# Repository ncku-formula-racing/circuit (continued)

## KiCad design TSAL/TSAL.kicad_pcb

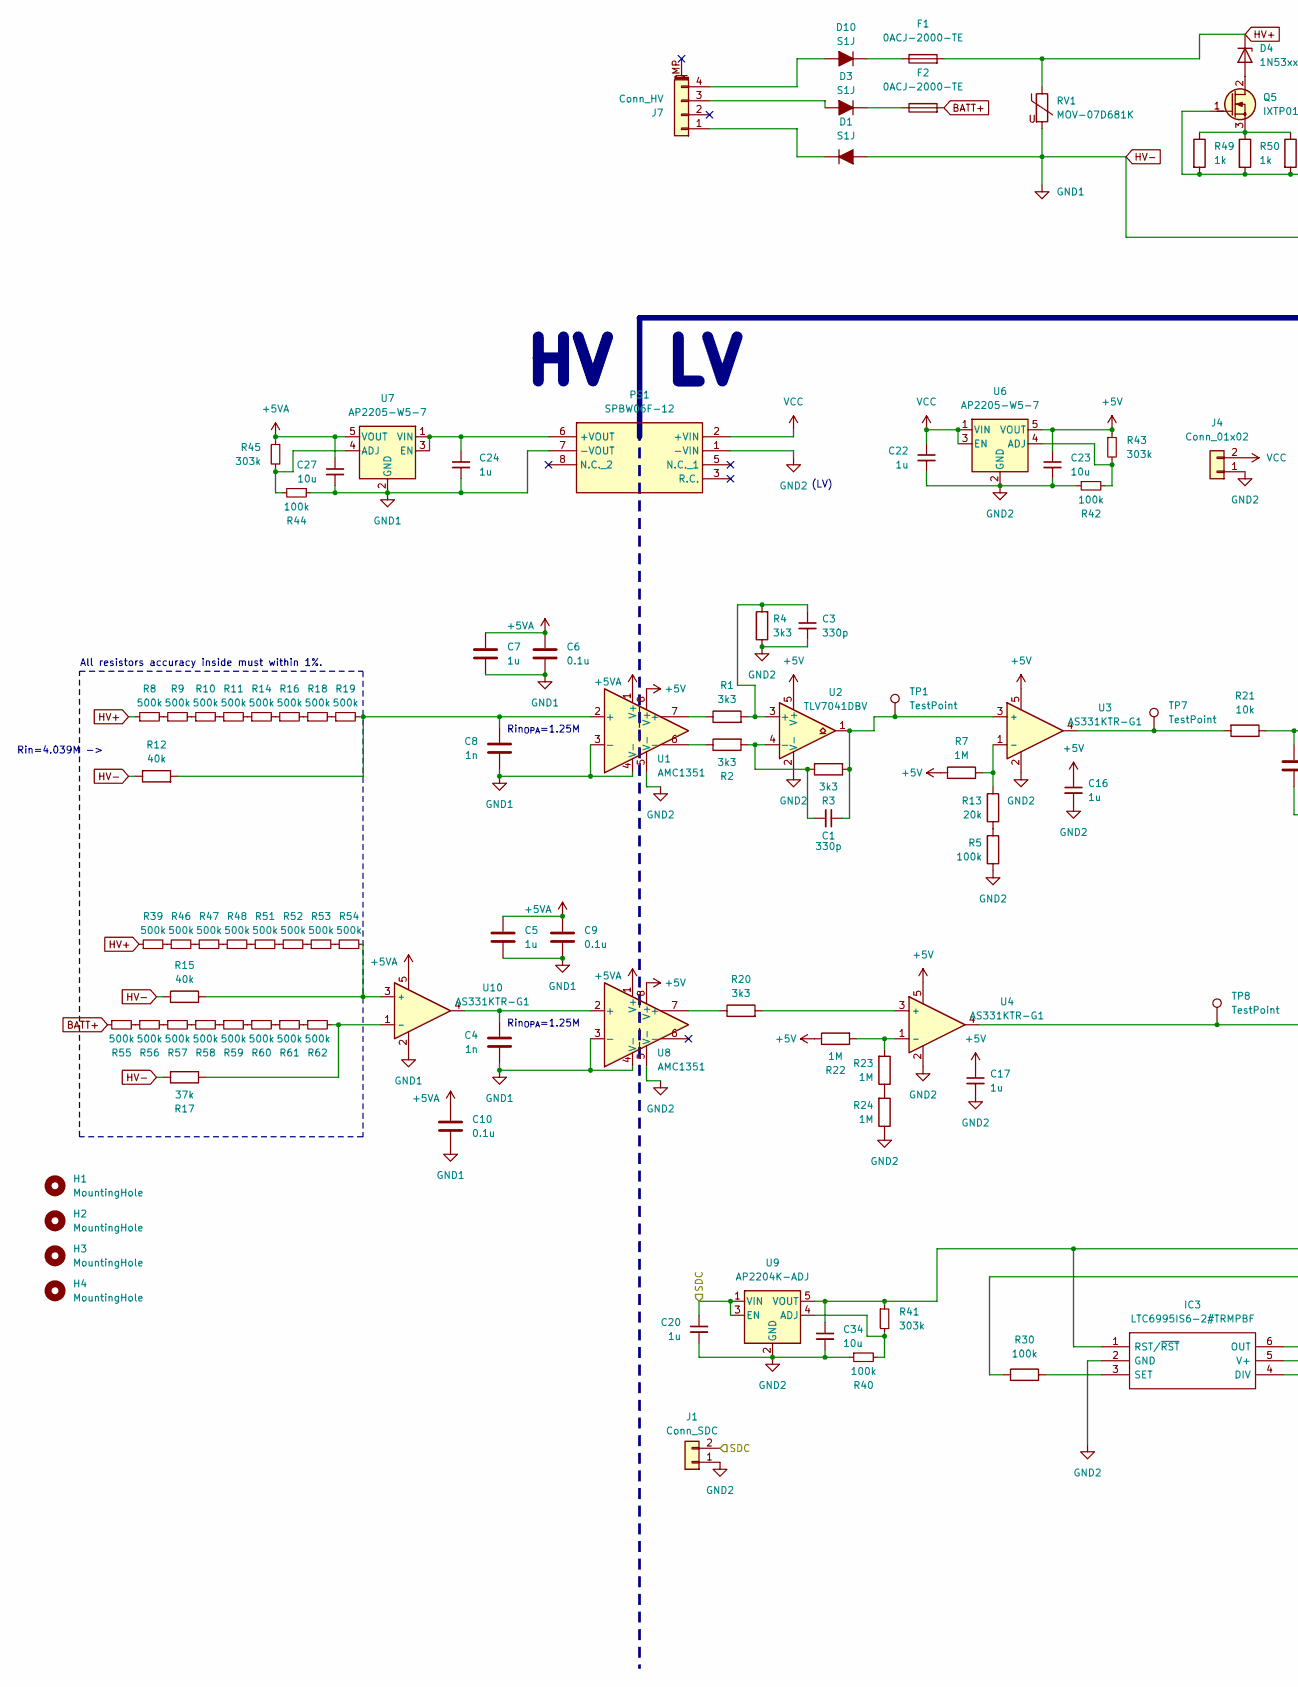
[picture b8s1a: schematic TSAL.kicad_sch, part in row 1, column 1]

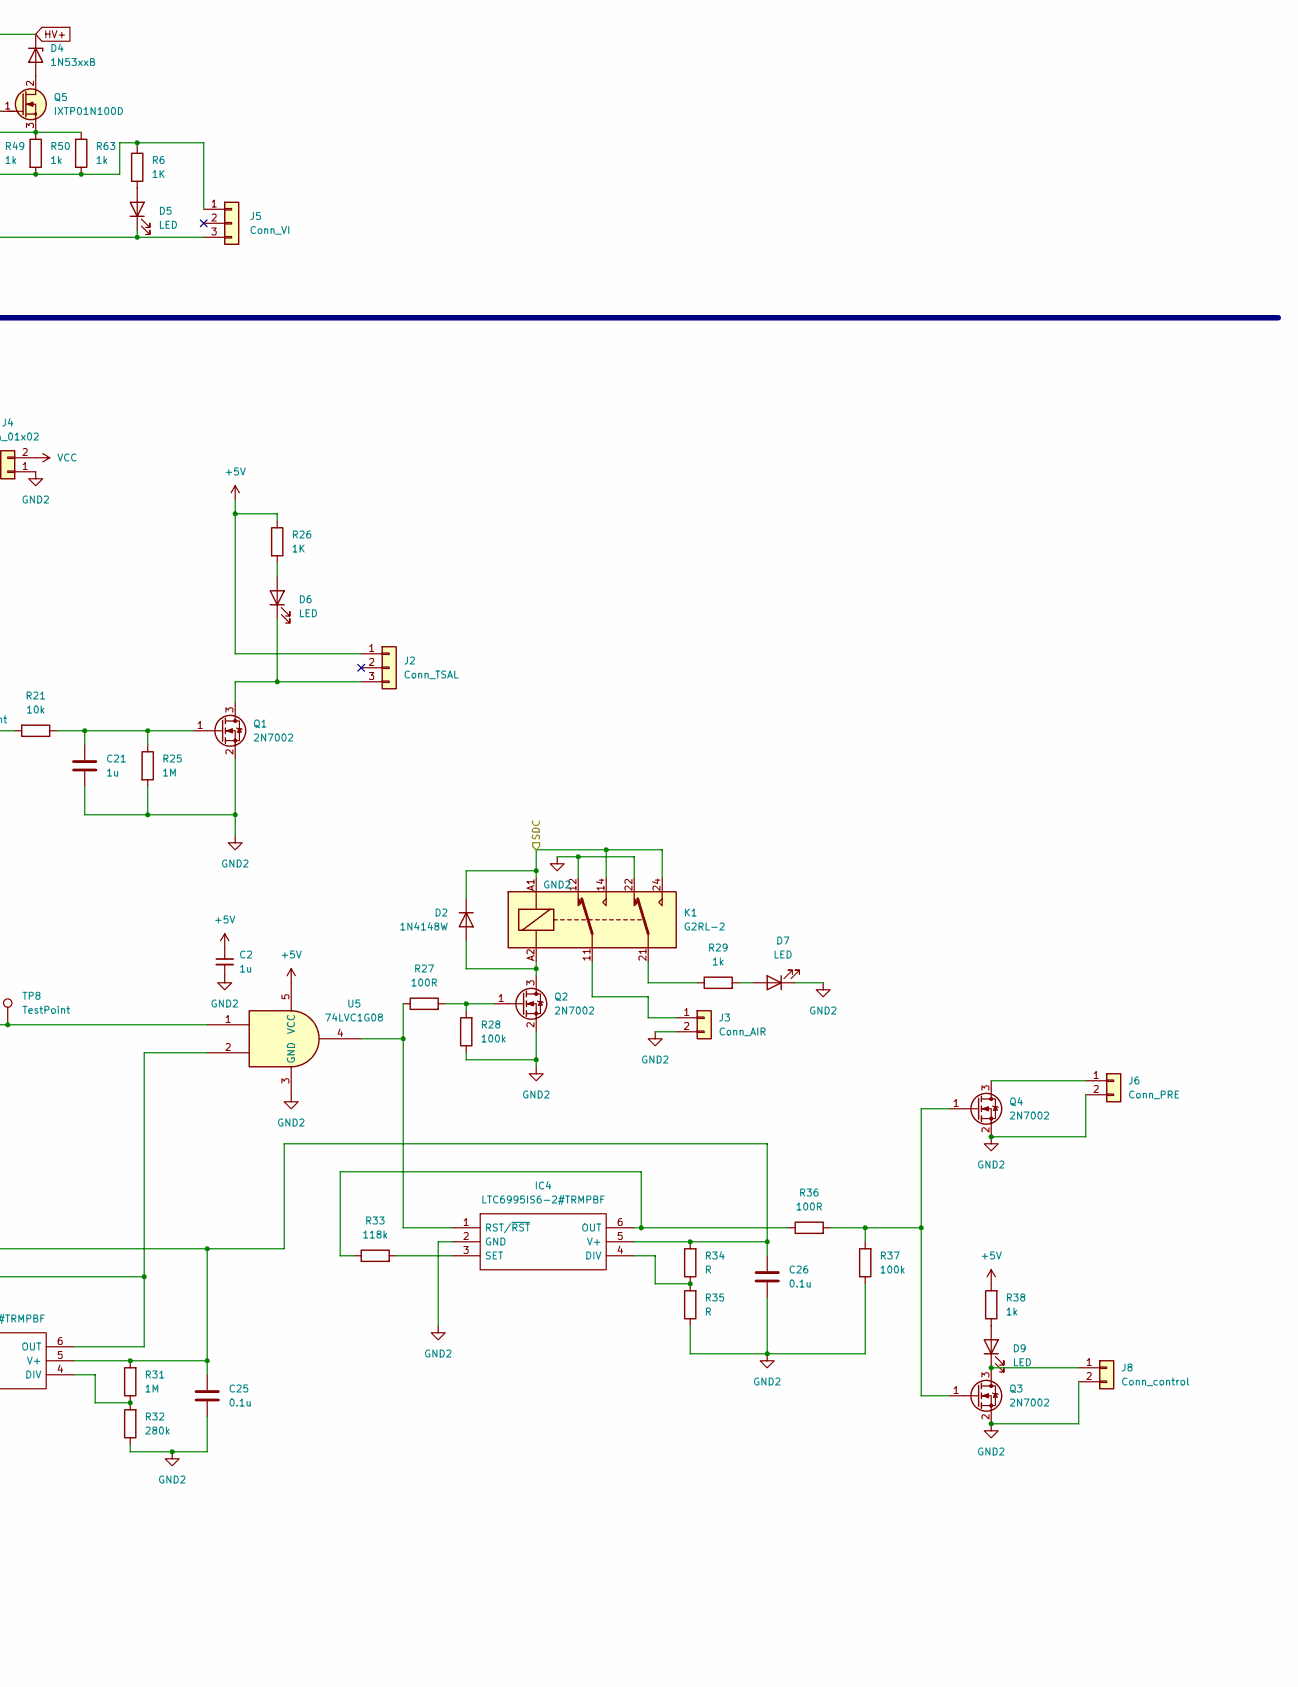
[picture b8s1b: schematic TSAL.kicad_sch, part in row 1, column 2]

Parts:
C1, C3: 330p; C_0603_1608Metric
C2, C5, C7, C16, C17, C20, C21, C22, C24: 1u; C_0603_1608Metric
C4, C8: 1n; C_0603_1608Metric
C6, C9, C10, C25, C26: 0.1u; C_0603_1608Metric
C23, C27, C34: 10u; C_0805_2012Metric
D1, D3, D10: S1J; D_SMA
D2: 1N4148W; D_SOD-123
D4: 1N53xxB; D_DO-201_P15.24mm_Horizontal
D5: LED; D_0805_2012Metric
D6, D7, D9: LED; LED_0805_2012Metric
F1, F2: 0ACJ-2000-TE; 0ACJ
H1, H2, H3, H4: MountingHole; MountingHole_3.2mm_M3_ISO14580
IC3, IC4: LTC6995IS6-2#TRMPBF; TSOT-23-6; Mouser Part Number 584-C6995IS6-2TRMPBF
J1: Conn_SDC; JST_XH_B2B-XH-A_1x02_P2.50mm_Vertical
J2: Conn_TSAL; JST_XH_B3B-XH-A_1x03_P2.50mm_Vertical
J3: Conn_AIR; JST_XH_B2B-XH-A_1x02_P2.50mm_Vertical
J4: Conn_01x02; JST_XH_B2B-XH-A_1x02_P2.50mm_Vertical
J5: Conn_VI; JST_XH_B3B-XH-A_1x03_P2.50mm_Vertical
J6: Conn_PRE; JST_XH_B2B-XH-A_1x02_P2.50mm_Vertical
J7: Conn_HV; Molex_Micro-Fit_3.0_43650-0424_1x04-1MP_P3.00mm_Vertical
J8: Conn_control; JST_XH_B2B-XH-A_1x02_P2.50mm_Vertical
K1: G2RL-2; Relay_DPDT_Omron_G2RL-2
PS1: SPBW06F-12; CONV_SPBW06F-12; Mouser Part Number 709-SPBW06F-12
Q1, Q2, Q3, Q4: 2N7002; SOT-23
Q5: IXTP01N100D; TO-220-3_Vertical
R1, R2, R3, R4, R20: 3k3; R_0603_1608Metric
R5, R28, R30, R37, R40, R42, R44: 100k; R_0603_1608Metric
R6, R26: 1K; R_0603_1608Metric
R7, R22, R23, R24, R25, R31: 1M; R_0603_1608Metric
R8, R9, R10, R11, R14, R16, R18, R19, R39, R46, R47, R48, R51, R52, R53, R54, R55, R56, R57, R58, R59, R60, R61, R62: 500k; R_0603_1608Metric
R12, R15: 40k; R_0603_1608Metric
R13: 20k; R_0603_1608Metric
R17: 37k; R_0603_1608Metric
R21: 10k; R_0603_1608Metric
R27, R36: 100R; R_0603_1608Metric
R29, R38: 1k; R_0603_1608Metric
R32: 280k; R_0603_1608Metric
R33: 118k; R_0603_1608Metric
R34, R35: R; R_0603_1608Metric
R41, R43, R45: 303k; R_0603_1608Metric
R49, R50, R63: 1k; R_0805_2012Metric
RV1: MOV-07D681K; RV_Disc_D9mm_W3.5mm_P5mm
TP1, TP7, TP8: TestPoint; TestPoint_THTPad_D1.5mm_Drill0.7mm
U1, U8: AMC1351; SOIC-8_7.5x5.85mm_P1.27mm
U2: TLV7041DBV; SOT-23-5
U3, U4, U10: AS331KTR-G1; SOT-23-5
U5: 74LVC1G08; SOT-23-5
U6, U7: AP2205-W5-7; SOT-23-5
U9: AP2204K-ADJ; SOT-23-5

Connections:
+5V: C2.1, C16.1, C17.1, C23.1, J2.1, R7.1, R22.1, R26.1, R38.2, R43.1, U1.8 (V+), U2.5 (V+), U3.5, U4.5, U5.5 (VCC), U6.5 (VOUT), U8.8 (V+)
+5VA: C5.1, C6.1, C7.1, C9.1, C10.1, C27.1, R45.1, U1.1 (V+), U7.5 (VOUT), U8.1 (V+), U10.5
/SDC: C20.1, D2.1 (K), J1.2, K1.14, K1.24, K1.A1, U9.1 (VIN), U9.3 (EN)
BATT+: F2.2, R55.1
GND2: C2.2, C3.2, C16.2, C17.2, C20.2, C21.2, C22.2, C23.2, C25.2, C26.2, C34.2, D7.1 (K), IC3.2 (GND), IC4.2 (GND), J1.1, J3.2, J4.1, J6.2, J8.2, K1.12, K1.22, PS1.1 (-VIN), Q1.2 (S), Q2.2 (S), Q3.2 (S), Q4.2 (S), R4.1, R5.1, R24.1, R25.2, R28.1, R32.1, R35.1, R37.1, R40.1, R42.1, U1.5 (V-), U2.2 (V-), U3.2, U4.2, U5.3 (GND), U6.2 (GND), U8.5 (V-), U9.2 (GND)
HV+: D4.1 (K), F1.2, R8.1, R39.1, RV1.1
HV-: C4.2, C5.2, C6.2, C7.2, C8.2, C9.2, C10.2, C24.2, C27.2, D1.2 (A), D5.1 (K), J5.3, PS1.7 (-VOUT), R12.1, R15.1, R17.2, R44.1, RV1.2, U1.3 (-), U1.4 (V-), U7.2 (GND), U8.3 (-), U8.4 (V-), U10.2
unnamed: C4.1, U8.2 (+), U10.4
unnamed: C8.1, R12.2, R19.2, U1.2 (+)
unnamed: D1.1 (K), J7.1
unnamed: D2.2 (A), K1.A2, Q2.3 (D)
unnamed: D3.2 (A), J7.3
unnamed: D3.1 (K), F2.1
unnamed: D4.2 (A), Q5.2 (D)
unnamed: D5.2 (A), R6.2
unnamed: D6.2 (A), R26.2
unnamed: D6.1 (K), J2.3, Q1.3 (D)
unnamed: D7.2 (A), R29.2
unnamed: D9.2 (A), R38.1
unnamed: D9.1 (K), J8.1, Q3.3 (D)
unnamed: D10.2 (A), J7.4
unnamed: D10.1 (K), F1.1
unnamed: IC3.4 (DIV), R31.1, R32.2
unnamed: IC3.6 (OUT), R30.1, U5.2
unnamed: C25.1, C26.1, C34.1, IC3.1 (RST/~RST), IC3.5 (V+), IC4.5 (V+), R31.2, R34.2, R41.1, U9.5 (VOUT)
unnamed: IC3.3 (SET), R30.2
unnamed: IC4.4 (DIV), R34.1, R35.2
unnamed: IC4.6 (OUT), R33.1, R36.1
unnamed: IC4.1 (RST/~RST), R27.1, U5.4
unnamed: IC4.3 (SET), R33.2
unnamed: J3.1, K1.11
unnamed: J5.1, Q5.1 (G), R6.1, R49.2, R50.2, R63.2
unnamed: J6.1, Q4.3 (D)
unnamed: K1.21, R29.1
unnamed: C24.1, PS1.6 (+VOUT), U7.1 (VIN), U7.3 (EN)
unnamed: C21.1, Q1.1 (G), R21.1, R25.1
unnamed: Q2.1 (G), R27.2, R28.2
unnamed: Q3.1 (G), Q4.1 (G), R36.2, R37.2
unnamed: Q5.3 (S), R49.1, R50.1, R63.1
unnamed: R1.1, U1.7 (+)
unnamed: R2.1, U1.6 (-)
unnamed: R8.2, R9.1
unnamed: R9.2, R10.1
unnamed: R10.2, R11.1
unnamed: R11.2, R14.1
unnamed: R5.2, R13.1
unnamed: R14.2, R16.1
unnamed: R16.2, R18.1
unnamed: R18.2, R19.1
unnamed: R20.1, U8.7 (+)
unnamed: R21.2, TP7.1, U3.4
unnamed: R23.1, R24.2
unnamed: R39.2, R46.1
unnamed: R46.2, R47.1
unnamed: R47.2, R48.1
unnamed: R48.2, R51.1
unnamed: R51.2, R52.1
unnamed: R52.2, R53.1
unnamed: R53.2, R54.1
unnamed: R55.2, R56.1
unnamed: R56.2, R57.1
unnamed: R57.2, R58.1
unnamed: R58.2, R59.1
unnamed: R59.2, R60.1
unnamed: R60.2, R61.1
unnamed: R61.2, R62.1
unnamed: TP8.1, U4.4, U5.1
unnamed: C3.1, R1.2, R4.2, U2.3 (+)
unnamed: C1.2, R2.2, R3.1, U2.4 (-)
unnamed: C1.1, R3.2, TP1.1, U2.1, U3.3 (+)
unnamed: R7.2, R13.2, U3.1 (-)
unnamed: R20.2, U4.3 (+)
unnamed: R22.2, R23.2, U4.1 (-)
unnamed: R42.2, R43.2, U6.4 (ADJ)
unnamed: R44.2, R45.2, U7.4 (ADJ)
unnamed: R40.2, R41.2, U9.4 (ADJ)
unnamed: R15.2, R54.2, U10.3 (+)
unnamed: R17.1, R62.2, U10.1 (-)
VCC: C22.1, J4.2, PS1.2 (+VIN), U6.1 (VIN), U6.3 (EN)

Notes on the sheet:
Rin=4.039M ->
Rin_{OPA}=1.25M
(LV)
All resistors accuracy inside must within 1%.

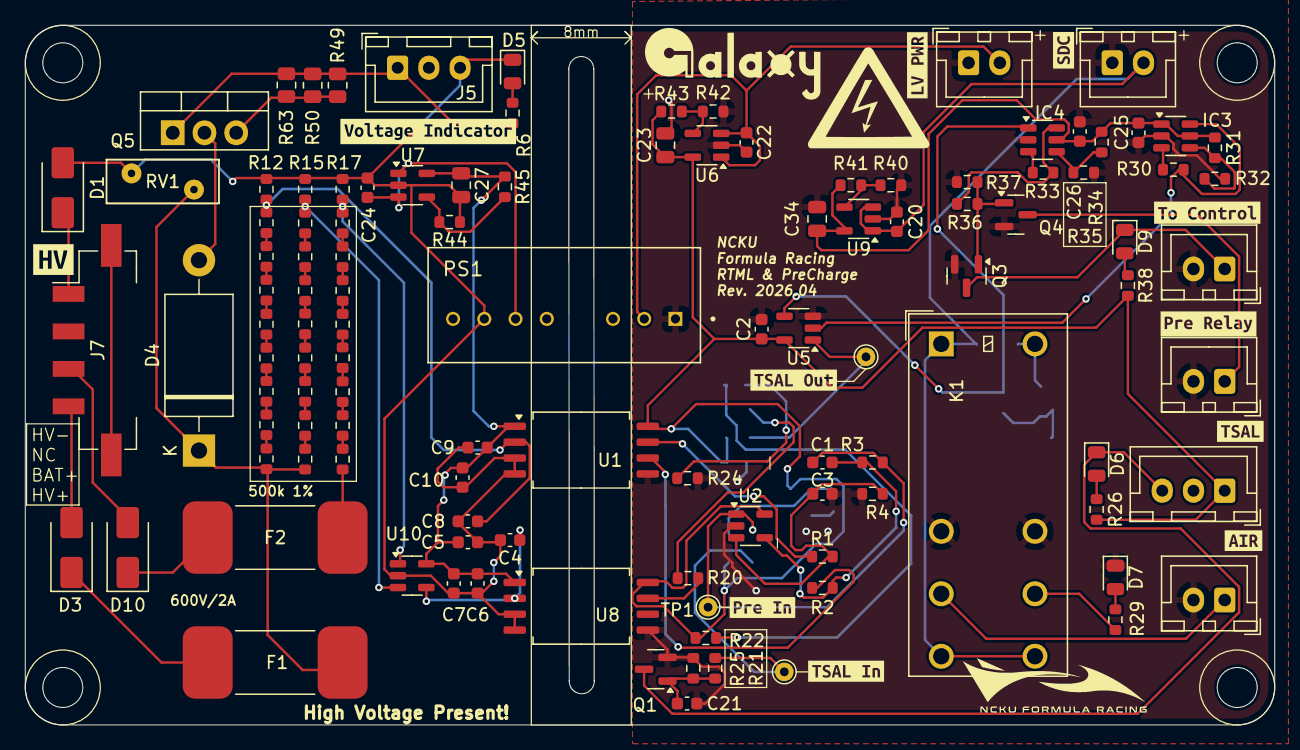
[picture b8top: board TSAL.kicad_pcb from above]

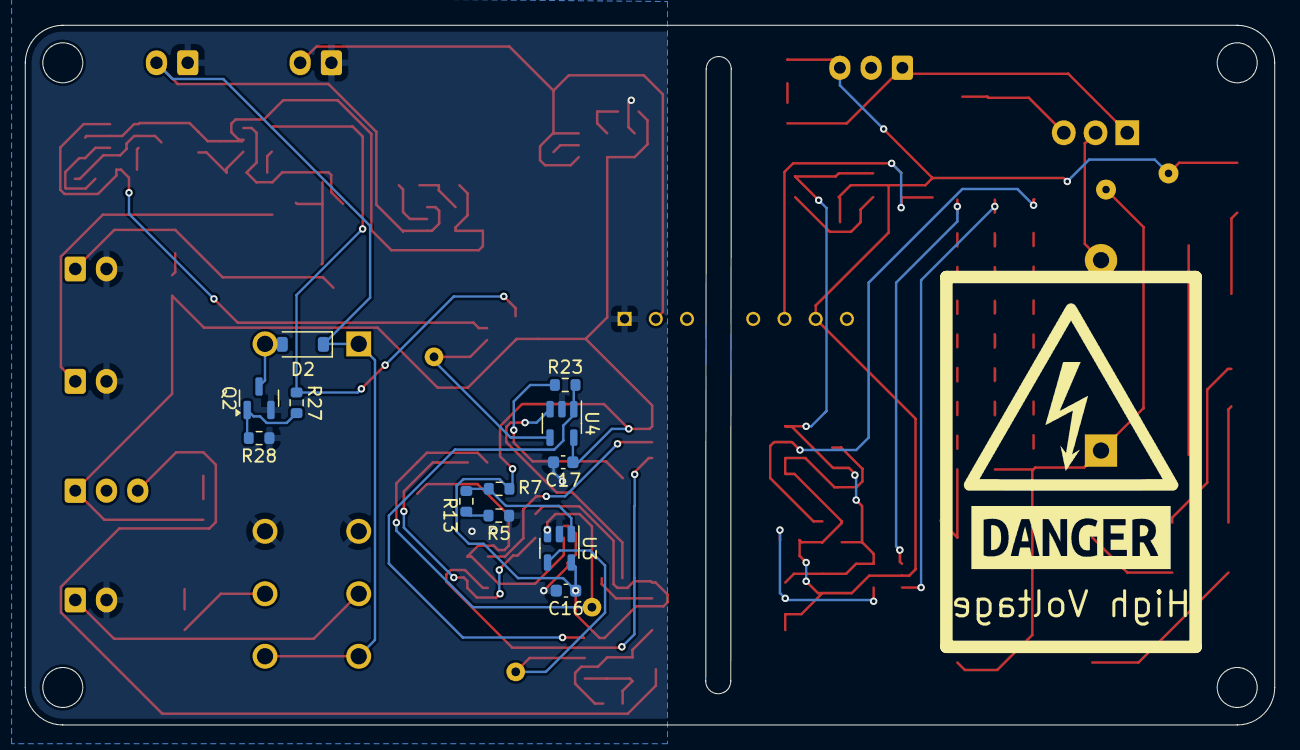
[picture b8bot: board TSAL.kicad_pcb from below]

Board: 2 copper layers, 100.0 x 56.0 mm, 142 parts (13 on the bottom side), 79 nets.

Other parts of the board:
kibuzzard-67A052A1: G***; kibuzzard-67A052A1
kibuzzard-67A0528E: G***; kibuzzard-67A0528E
kibuzzard-67A05267: G***; kibuzzard-67A05267
kibuzzard-6788E0FE: G***; kibuzzard-6788E0FE
kibuzzard-67872F86: G***; kibuzzard-67872F86
kibuzzard-67872F94: G***; kibuzzard-67872F94
kibuzzard-67879B82: G***; kibuzzard-67879B82
kibuzzard-678721F1: G***; kibuzzard-678721F1
kibuzzard-6787964A: G***; kibuzzard-6787964A
kibuzzard-67872213: G***; kibuzzard-67872213
kibuzzard-67879350: G***; kibuzzard-67879350
kibuzzard-67888934: G***; kibuzzard-67888934

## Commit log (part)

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2025-03-01 Add gitignore
2025-03-01 Add bms slave board
2025-03-01 Add bms master
2025-03-01 Add SDC
2025-03-01 feat(bms master): current sensor circuits
2025-03-01 Finish bms_master pcb layout
2025-03-02 Add silkscreen labels and revision number
2025-03-02 Reconfigure file structure and create share lib and 3D CAD
2025-03-02 fix: rename 3D files path
2025-03-03 chore: improve routing
2025-03-03 fix: add bms fault connector
2025-03-03 Set basic dimension of the board and some simple layout
2025-03-04 Finish slave basic layout, will be tweaked later on
2025-03-04 Finish route width and thermal pad tweaking, waited to be label and marked
2025-03-04 Add team logo to share folder
2025-03-05 Add team logo to the board
2025-03-05 Add label of connectors, test points
2025-03-05 Put logo image file to folder "Logo_Lib"
2025-03-06 Connect main chip's pad to GND and put vias through holes
2025-03-08 bspd v.3
2025-03-08 BSPD_test
2025-03-08 BSPD v3 finish basic layout
2025-03-08 SDC add pinheader
2025-03-09 feat: add logo
2025-03-09 feat: improve bms thermal performance
2025-03-09 Add And gate and R at limit chack
2025-03-09 Change JST to pin header
2025-03-09 Change JST to pinheader
2025-03-10 Add DAQ circuit
2025-03-10 update cooling DAQ
2025-03-11 fix: improve GND plant
2025-03-11 finish DAQ ver.1
2025-03-11 finish DAQ ver.2
2025-03-12 fix: improve pcb layout
2025-03-12 chore: rename folder
2025-03-12 update DAQ
2025-03-12 feat: use 2x10 pin
2025-03-12 BSPD v.3.2 change pin header to 02*10
2025-03-12 feat: improve diff signal
2025-03-12 Change some design errors
2025-03-12 modify some label
2025-03-12 feat: add miniAIR
2025-03-12 feat: add imu base board
2025-03-13 feat: add TSAL
2025-03-13 feat: add main hoop light
2025-03-15 feat: add fuse box
2025-03-15 feat: add stencil
2025-03-15 remove 12V LDO
2025-03-15 add back_mcu folder
2025-03-16 feat: improve buck feedback
2025-03-16 change J5 connector
2025-03-16 Add sd card to BMS master and change commu to UART
2025-03-16 Link sd card slot to footprint
2025-03-16 add USB connector and modify footprints
2025-03-16 layout
2025-03-16 Redo BMS master layout again, SD card slot added
2025-03-16 Further update layout detail to improve clearance
2025-03-16 feat: add dashboard
2025-03-16 refill zone
2025-03-16 add 0317 output file
2025-03-16 add zip file
2025-03-16 fix: adjust daq layout
2025-03-17 finish layout
2025-03-18 remove output
2025-03-18 feat: add apps
2025-03-18 chore: change XTR117 footprint
2025-03-22 add mainboard
2025-03-28 add layout
2025-04-19 fix CAN IC, modify pump_PWR, fix Cu length label
2025-04-19 recover PUMP_PWR
2025-04-19 add mounting hole
2025-04-20 add: TSSI modify: CAN
2025-04-21 modify: decouple capacitor
2025-04-21 Fix bms master can bus tx/rx opposite issue
2025-04-21 Update revision information on schemetic and pcb blueprint
2025-04-25 fix: reverse the input logic
2025-04-25 chore: remove pull up resistor and change flyback diodes
2025-04-28 feat: change iso OPA type and preC. circuit
2025-04-28 chore: basic section of layout
2025-04-30 v2025.5
2025-05-09 finish v2025.5
2025-05-17 fix: optimize VI schematics
2025-05-20 v2025.5 finish schemetic
2025-05-23 feat: add control board
2025-05-28 fix: power symbol and connector
2025-05-30 feat: implement apps pcb
2025-05-30 fix: CAN pin error
2025-05-30 fix: can jumper
2025-06-05 add charger v.1
2025-06-08 charger mainboard v2025.6
2025-06-08 v2025.6, add vdd to accbox
2025-06-08 add groung conn
2025-06-14 refill cu zone
2025-06-14 chore: ignores gerber files
    Prevents unnecessary tracking of build output files.
2025-06-26 modify LDO resistor
2025-06-29 feat: implement schematic and select footprints
2025-07-03 fix(ctrl_board): correct 100nF cap footprint
    100nF capacitor footprint should be 0603 but using 0402 originally.
2025-07-22 fix: use DXT5551P5 to increase power and remove onboard NTC
2025-07-23 change comparator to AS331KTR-G1
2025-07-23 add AS331KTR-G1 scemetic symbol
2025-07-25 feat: add LoRa module footprint and 3D
2025-07-25 feat: wireless BMS and USB power
2025-07-26 feat: implement control board layout
2025-07-26 fix(ctrl-board): add label on PCB
2025-07-30 feat: LVBMS schematics
2025-07-30 add pull up Resistor
2025-07-30 add AS331KTR-G1
2025-07-30 modify comparator
2025-07-31 add LM2903QS-13
2025-07-31 v2025.07
2025-07-31 remove gnd from conn
2025-08-02 v2025.8
2025-08-03 feat: LV BMS layout
2025-08-03 v2025.8 but need to add another DAQ
2025-08-03 change comparator
2025-08-03 modify LM2903QS-13
2025-08-09 add Brake-light
2025-09-05 fix: USB and USART traces
2025-09-14 feat: redesign control board
2025-09-17 control-board: update Ver 2025.9-1
2025-09-18 chore: upload connector 3D CAD
2025-09-27 modify: control board schematic
2025-09-29 add: 74650074 footprint
2025-10-02 v2025.10 :user friendly ver.
2025-10-02 v2025.10 schematic
2025-10-02 sdc_mcu v2025.10 schematic
2025-10-03 modify: control board
2025-10-04 modify: diodes and JST footprint
2025-10-04 modify: add 5V power
2025-10-07 v2025.10
2025-10-07 chore: add control board pdf
2025-10-08 fix:add pull up resistors to comparators
2025-10-09 feat : BrakeLight layout
2025-10-09 feat:M8 connect 3D model
2025-10-09 feat:SMA RF 3D model
2025-10-10 fix: SWDIO LED
2025-10-10 fix: SWDIO LED & CAN jumper
2025-10-11 fix: mounting hole
2025-10-11 chore: rename directory
2025-10-11 fix: re-layout with 4 layers board
2025-10-14 add: pdf
2025-10-15 feat: relayout sdc mcu
2025-10-15 feat: add ESD in CAN
2025-12-04 feat: Stop Developed file
2025-12-05 feat: update schematic & adc
2025-12-06 feat: unfinished lv-mainboard
2025-12-08 feat: lv main board
2025-12-23 feat: add RC filter for brake light
2025-12-23 feat: lv-mainboard v2025.12
2025-12-28 feat: Replace PreC resistor by LPS300
2025-12-29 black-box: init
2025-12-30 modify: replace SDC pwr with P8
2025-12-30 black-box: update
2025-12-30 black-box: add WS2812 & 3D model
2025-12-30 black-box: modify layout
2026-01-17 Charger v2026.1
2026-01-18 fix: resistor of SDC_MCU
2026-01-26 V2026.01: fix: USB pin and some issues
2026-01-26 feat: flip one side of the LED matrix
2026-01-30 feat: README version of LVBMS
2026-02-11 fix: update resistor
2026-02-25 update the version of APPS
2026-02-25 feat: update control-board output pdf
2026-02-28 feat: add can esd
2026-03-24 fix: repair pin
2026-04-02 layout done
2026-04-02 fix: replace NMOS and div resistors
2026-04-03 Create discharge file
2026-04-03 finish discharge layout
2026-04-03 create relay footprint file
2026-04-03 Create 5503121 (relay used in discharge) file
2026-04-03 add discharge relay footprint
2026-04-04 finish mainhoop-light layout
2026-04-04 chore: reduce board size and increase trace width
2026-04-05 feat: combine 2 disC into PCB
2026-04-06 fix distance between pad to led
2026-04-06 change the pads' size
2026-04-07 create timer file
2026-04-07 upload triangular pyramid timer
2026-04-07 feat: complete panel sch
2026-04-07 feat: complete bms panel layout
2026-04-07 fix: panel channel A0 & B15
2026-04-08 fix: change direction of pinheader
2026-04-08 fix: panel layout
2026-04-08 fix: remove filled zone
2026-04-09 fix: update version of RTML
2026-04-12 add timer
2026-04-12 finish timer layout
2026-04-16 feat: bms slave layout
2026-04-23 fix: replace PMOS, resistor and pull-up of RTML
2026-04-23 fix: CAN bus pin error
2026-04-30 fix: fuse & tvs package
2026-05-03 update datalogger buck converter
2026-05-06 feat: add DCDC and fix layout
2026-05-15 modify discharge ver2
2026-05-19 fix: move flyback diode position
2026-05-20 feat: redesign
2026-05-21 fix: dashboard CAN
